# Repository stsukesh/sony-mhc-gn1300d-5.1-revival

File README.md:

# Sony MHC-GN1300D 5.1 Audio System Revival

A complete, production-grade revival and modernization system for the vintage **Sony MHC-GN1300D Mini Hi-Fi Component System** (and similar 5.1 home theater units). 

This project replaces dead, obsolete hybrid IC amplifier boards (STK modules) and failing logic boards with a **single custom 150×200mm 2-layer PCB**, modern high-efficiency Class-D amplification, an active analog crossover, an ESP32 IoT control hub, and a multi-layer hardware-software fail-proof protection engine.

---

## Key System Specifications

| Parameter | Specification |
|---|---|
| **Form Factor** | 150 mm × 200 mm 2-Layer PCB (Lion Circuits India compatible) |
| **Output Channels** | 5.1 Channels (Front L/R, Surround L/R, Center, Subwoofer) |
| **Amplifier ICs** | 3× Texas Instruments TPA3116D2 Class-D stereo amplifiers |
| **Crossover Network** | Analog 2nd-order Sallen-Key active crossover (80 Hz cutoff, 3× NE5532 op-amps) |
| **Microcontroller** | ESP32-WROOM-32 (240 MHz dual-core, WiFi, BLE) |
| **Volume Control** | Microchip MCP4252 SPI 8-bit dual digital potentiometer |
| **Input Selection** | TI CD4052 dual 4:1 multiplexer (Bluetooth, 3.5mm AUX, USB Audio) |
| **Local Interface** | 2.42" SSD1309 SPI OLED (128×64) + Rotary Encoder + TSOP1738 IR Remote |
| **Connectivity** | WiFi AP (`Sony5.1-Revival`) & STA, Web dashboard, REST API, WebSockets, UART CLI |
| **Power Supply** | 230V AC mains input, internal 18V AC toroidal transformer, KBU810 bridge + 2× 4700µF filter (~24V DC), LM2596-5.0 buck, AMS1117-3.3 LDO, TLE2426 virtual ground |
| **Protection** | 5-layer fail-safe: DC offset detect, heatsink NTC thermal sensing, SPST 10A relay, polyfuses, HW pull-downs |
| **Total Build Cost** | ~₹9,124 INR (~$110 USD) — well within ₹10,000 budget |

---

## 5-Layer Fail-Proof Protection Engine

1. **Layer 1 — Hardware Fail-Safe Defaults:**
   - Amps default to hardware-muted via 10kΩ pull-downs on `/MUTE`.
   - Speaker 24V supply is isolated via normally-open relay `K1`. If the ESP32 crashes or loses power, speakers remain 100% silent and protected.
2. **Layer 2 — Hardware Watchdog Timer (TWDT):**
   - 10-second timeout automatically hard-resets the MCU into a safe state if firmware hangs.
3. **Layer 3 — Timed Startup Sequencing:**
   - 3-second power-on delay to stabilize rails, fault pin verification, relay closure, and a 500ms delayed un-mute to completely eliminate turn-on thumps.
4. **Layer 4 — Continuous Runtime ADC Telemetry:**
   - Sub-millivolt DC offset detection on speaker outputs (`GPIO36`).
   - Heatsink thermal monitoring via 10kΩ NTC thermistor (`GPIO35`): auto-attenuation at >60°C, emergency shutdown at >80°C.
   - Continuous latching on all 3 TPA3116D2 `/FAULT` lines (`GPIO32`, `GPIO33`, `GPIO34`).
5. **Layer 5 — Output Polyfuse Current Clamping:**
   - 2A resettable PTC polyfuses in series with speaker outputs to protect against external voice coil shorts.

---

## Repository Structure

```
├── hardware/
│   └── sony-5.1-revival/
│       ├── sony-5.1-revival.kicad_pro      # KiCad 10 Project File
│       ├── sony-5.1-revival.kicad_sch      # Top-level Hierarchical Schematic
│       ├── power_supply.kicad_sch          # Sheet 1: AC-DC, Buck, LDO & Virtual Ground
│       ├── amplifier.kicad_sch             # Sheet 2: 3× TPA3116D2 Class-D Stages
│       ├── crossover_input.kicad_sch       # Sheet 3: CD4052 Mux, MCP4252 Vol & NE5532 Filters
│       ├── controller.kicad_sch            # Sheet 4: ESP32, OLED, Rotary, IR, USB UART
│       ├── protection.kicad_sch            # Sheet 5: Relay, NTC, DC Sense, Screw Terminals
│       ├── sony-5.1-revival.kicad_pcb      # Fully placed & routed 150×200mm 2-layer PCB
│       ├── sony-5.1-revival-schematic.pdf  # Clean multi-page vectorized schematic
│       ├── pcb_preview_top.png             # High-resolution 300 DPI board render
│       ├── BOM.csv                         # Itemized 38-part Bill of Materials (INR)
│       ├── lioncircuits_fab_files.zip      # Ready-to-upload Gerber/Drill manufacturing zip
│       ├── gerbers/                        # Unpacked Gerber and drill files
│       └── libs/                           # Custom KiCad symbol library
├── firmware/
│   ├── platformio.ini                      # PlatformIO build configuration for ESP32
│   ├── src/
│   │   ├── main.cpp                        # System orchestrator and startup sequencing
│   │   ├── config.h                        # System parameters and protection thresholds
│   │   ├── pin_definitions.h               # Complete GPIO & SPI pin map
│   │   ├── audio_controller.cpp / .h       # MCP4252 digital pot and CD4052 mux driver
│   │   ├── display_manager.cpp / .h        # 2.42" SSD1309 OLED graphics engine
│   │   ├── input_handler.cpp / .h          # Rotary encoder (ISR) & NEC IR remote decoder
│   │   ├── protection.cpp / .h             # 5-layer telemetry and emergency shutdown engine
│   │   ├── web_server.cpp / .h             # Async web server, REST API & WebSockets
│   │   ├── serial_cmd.cpp / .h             # 115,200 baud UART command interface
│   │   └── wifi_manager.cpp / .h           # Dual AP/STA WiFi manager with NVS storage
│   └── data/
│       └── index.html                      # Responsive dark-theme browser dashboard
├── tools/                                  # Project automation, simulation & generators
├── MHC-GN1300D-Revival-Master-Plan.md      # Comprehensive architecture & wiring manual
├── Sony-5.1-Revival-Implementation-Report.md # Full design report and telemetry analysis
├── Sony-5.1-Revival-OEM-Service-Manual.md  # OEM-grade repair, schematics & troubleshooting guide
└── Lion-Circuits-Fabrication-and-Assembly-Manual.md # PCB fabrication & bench checkout guide
```

---

## PCB Fabrication Guide (Lion Circuits India)

The board layout is pre-configured and checked against Lion Circuits manufacturing capabilities:

1. Upload `hardware/sony-5.1-revival/lioncircuits_fab_files.zip` directly to [LionCircuits.com](https://www.lioncircuits.com/).
2. Specify the fabrication parameters:
   - **Dimensions:** 150.0 mm × 200.0 mm
   - **Layers:** 2 Layers
   - **PCB Thickness:** 1.6 mm
   - **Copper Weight:** 1 oz (35 µm)
   - **Solder Mask:** Green (or Matte Black)
   - **Silkscreen:** White
   - **Surface Finish:** HASL Lead-Free
3. Minimum trace width used: **0.30 mm** (Signal), **1.00 mm - 3.50 mm** (Power / Speaker).
4. Minimum clearance: **0.25 mm** (High-voltage AC clearance: > 5.0 mm).

---

## Firmware Setup & Flashing

### Prerequisites
- [PlatformIO Core](https://platformio.org/install/cli) or VS Code with PlatformIO IDE extension.
- Micro-USB cable connected to the ESP32 development board.

### Build and Upload
```bash
cd firmware

# Build firmware binary
pio run

# Upload to ESP32 (auto-detects port)
pio run -t upload

# Upload SPIFFS/LittleFS web dashboard assets
pio run -t uploadfs

# Open serial terminal monitor (115200 baud)
pio device monitor -b 115200
```

### Serial Control Interface
Connect any serial terminal at `115200 baud, 8-N-1`:
- `VOL <0-255>`: Set volume directly
- `VOL+` / `VOL-`: Adjust volume up/down by 5 steps
- `INPUT <BT|AUX|USB>`: Switch input audio source
- `MUTE`: Toggle mute
- `POWER`: Toggle 24V amplifier relay
- `STATUS`: Print full JSON telemetry report
- `PROTECTION`: Display ADC offsets, temperatures, and fault latch states

---

## License & Safety Disclaimer

**Mains Voltage Warning:** This design incorporates 230V AC mains input. Always disconnect AC mains before touching any part of the primary side. Use an isolation transformer during bench testing.

Licensed under the [MIT License](LICENSE).

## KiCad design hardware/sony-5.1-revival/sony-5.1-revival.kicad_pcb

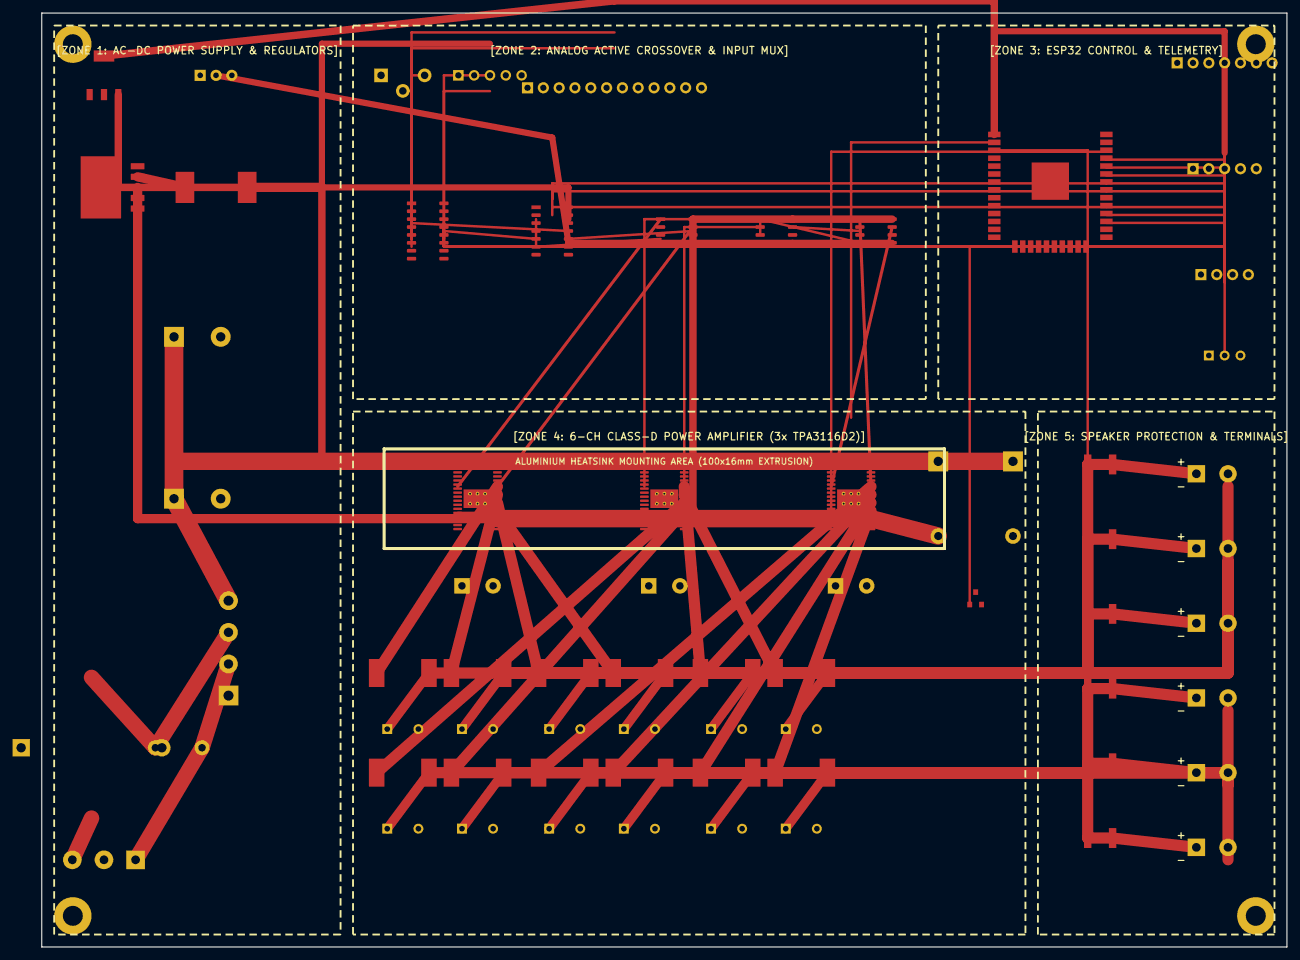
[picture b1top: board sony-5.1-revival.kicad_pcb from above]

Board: 2 copper layers, 200.0 x 150.0 mm, 71 parts (0 on the bottom side), 52 nets.

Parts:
BR1: KBU810_8A; Diode_Bridge_Vishay_KBU
C1, C2: 4700uF_35V; CP_Radial_D18.0mm_P7.50mm
C_BULK1, C_BULK2, C_BULK3: CP_Radial_D12.5mm_P5.00mm
C_O1, C_O2, C_O3, C_O4, C_O5, C_O6, C_O7, C_O8, C_O9, C_O10, C_O11, C_O12: C_Rect_L7.2mm_W4.5mm_P5.00mm_FKS2_FKP2_MKS2_MKP2
F1: 3A_250V; Fuseholder_5x20mm
H: MountingHole_3.2mm_M3
H#2, H#3, H#4: MountingHole_3.2mm_M3
J_AC: 230V_AC_IN; TerminalBlock_1x03_P5.08mm
J_AUX: AUX_3.5mm; Jack_3.5mm_CUI_SJ1-3523N_Horizontal
J_CTRL: UART_CONTROL; PinHeader_1x04_P2.54mm_Vertical
J_ENC: ROTARY_ENCODER; PinHeader_1x05_P2.54mm_Vertical
J_OLED: 2.42_SSD1309_SPI; PinHeader_1x07_P2.54mm_Vertical
J_SPK_C: CENTER; TerminalBlock_1x02_P5.08mm
J_SPK_FL: FRONT_LEFT; TerminalBlock_1x02_P5.08mm
J_SPK_FR: FRONT_RIGHT; TerminalBlock_1x02_P5.08mm
J_SPK_SL: SURROUND_LEFT; TerminalBlock_1x02_P5.08mm
J_SPK_SR: SURROUND_RIGHT; TerminalBlock_1x02_P5.08mm
J_SPK_SUB: SUBWOOFER; TerminalBlock_1x02_P5.08mm
J_USB_IN: USB_AUDIO_DAC; PinHeader_1x05_P2.54mm_Vertical
K1: RELAY_10A_24V; Relay_SPST_SANYOU_SRD_Series_Form_A
L1, L2, L3, L4, L5, L6, L7, L8, L9, L10, L11, L12: 22uH_5A; L_10.4x10.4_H4.8
L_BUCK: 33uH_3A; L_12x12mm_H8mm
PF_C: 2A_PTC; Fuse_1812_4532Metric
PF_FL: 2A_PTC; Fuse_1812_4532Metric
PF_FR: 2A_PTC; Fuse_1812_4532Metric
PF_SL: 2A_PTC; Fuse_1812_4532Metric
PF_SR: 2A_PTC; Fuse_1812_4532Metric
PF_SUB: 2A_PTC; Fuse_1812_4532Metric
Q1: SOT-23
RV1: 14D431K; RV_Disc_D14mm_W4.5mm_P7.5mm
U_AMP1: TPA3116_FL_FR; HTSSOP-32-1EP_6.1x11mm_P0.65mm_EP3.1x6.1mm_ThermalVias
U_AMP2: TPA3116_SL_SR; HTSSOP-32-1EP_6.1x11mm_P0.65mm_EP3.1x6.1mm_ThermalVias
U_AMP3: TPA3116_C_SUB; HTSSOP-32-1EP_6.1x11mm_P0.65mm_EP3.1x6.1mm_ThermalVias
U_BT: QCC3008_BT5.0; PinHeader_1x12_P2.54mm_Vertical
U_BUCK: LM2596-5.0; TO-263-5_TabPin3
U_IR: IRReceiver_Vishay_CAST-3pin
U_LDO: AMS1117-3.3; SOT-223-3_TabPin2
U_MCU: ESP32-WROOM-32
U_MUX: CD4052_MUX; SOIC-16_3.9x9.6mm_P1.27mm
U_OP1: NE5532_HPF; SOIC-8_3.9x4.8mm_P1.27mm
U_OP2: NE5532_SUM; SOIC-8_3.9x4.8mm_P1.27mm
U_OP3: NE5532_LPF_C; SOIC-8_3.9x4.8mm_P1.27mm
U_VGND: TLE2426; TO-92_Inline
U_VOL: MCP4252_POT; SOIC-14_3.9x8.4mm_P1.27mm

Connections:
AC_LIVE: BR1.2, F1.1, F1.2, J_AC.1, RV1.1
AC_NEUTRAL: BR1.3, J_AC.3, RV1.2
AUDIO_L_RAW: U_MUX.13, U_VOL.5
AUDIO_R_RAW: U_MUX.3, U_VOL.10
BT_KEY: U_BT.5, U_MCU.30
BT_OUT_L: U_BT.3, U_MUX.12
BT_OUT_R: U_BT.4, U_MUX.1
ENC_A: J_ENC.5, U_MCU.36
ENC_B: J_ENC.4, U_MCU.35
ENC_SW: J_ENC.3, U_MCU.34
GND: BR1.4, C1.2, C2.2, C_BULK1.2, C_BULK2.2, C_BULK3.2, C_O1.2, C_O2.2, C_O3.2, C_O4.2, C_O5.2, C_O6.2, C_O7.2, C_O8.2, C_O9.2, C_O10.2, C_O11.2, C_O12.2, H.1, H#2.1, H#3.1, H#4.1, J_AC.2, J_AUX.1, J_CTRL.4, J_ENC.1, J_OLED.1, J_USB_IN.2, J_USB_IN.5, Q1.2, U_AMP1.1, U_AMP1.5, U_AMP1.6, U_AMP1.9, U_AMP1.10, U_AMP1.11, U_AMP1.13, U_AMP1.15, U_AMP1.16, U_AMP1.17, U_AMP1.19, U_AMP1.25, U_AMP1.31, U_AMP1.33, U_AMP2.1, U_AMP2.5, U_AMP2.6, U_AMP2.9, U_AMP2.10, U_AMP2.11, U_AMP2.13, U_AMP2.15, U_AMP2.16, U_AMP2.17, U_AMP2.19, U_AMP2.25, U_AMP2.31, U_AMP2.33, U_AMP3.1, U_AMP3.5, U_AMP3.6, U_AMP3.9, U_AMP3.10, U_AMP3.11, U_AMP3.13, U_AMP3.15, U_AMP3.16, U_AMP3.17, U_AMP3.19, U_AMP3.25, U_AMP3.31, U_AMP3.33, U_BT.2, U_BT.6, U_BT.7, U_BT.8, U_BT.9, U_BT.10, U_BT.11, U_BT.12, U_BUCK.3, U_BUCK.5, U_BUCK.6, U_IR.2, U_LDO.1, U_MCU.1, U_MCU.4, U_MCU.7, U_MCU.8, U_MCU.9, U_MCU.10, U_MCU.11, U_MCU.12, U_MCU.13, U_MCU.14, U_MCU.16, U_MCU.17, U_MCU.18, U_MCU.21, U_MCU.22, U_MCU.25, U_MCU.26, U_MCU.31, U_MCU.39, U_MUX.4, U_MUX.6, U_MUX.7, U_MUX.8, U_MUX.11, U_OP1.4, U_OP2.4, U_OP3.4, U_VGND.3, U_VOL.4
HPF_L: U_AMP1.4, U_OP1.1, U_OP1.2, U_OP2.2
HPF_R: U_AMP1.14, U_OP1.6, U_OP1.7
IR_RECV: U_IR.1, U_MCU.37
J_AUX_L: J_AUX.2, U_MUX.14
J_AUX_R: J_AUX.3, U_MUX.5
MUTE_ALL: U_AMP1.12, U_AMP2.12, U_AMP3.12, U_MCU.38
MUX_A: U_MCU.24, U_MUX.10
OLED_CS: J_OLED.7, U_MCU.20
OLED_DC: J_OLED.6, U_MCU.19
OUT_CENTER: U_AMP3.4, U_OP3.7
OUT_C_N: C_O10.1, J_SPK_C.2, L10.1, L10.2, U_AMP3.18, U_AMP3.24
OUT_C_P: C_O9.1, J_SPK_C.1, L9.1, L9.2, PF_C.1, PF_C.2, U_AMP3.20, U_AMP3.21
OUT_FL_N: C_O2.1, J_SPK_FL.2, L2.1, L2.2, U_AMP1.18, U_AMP1.24
OUT_FL_P: C_O1.1, J_SPK_FL.1, L1.1, L1.2, PF_FL.1, PF_FL.2, U_AMP1.20, U_AMP1.21
OUT_FR_N: C_O4.1, J_SPK_FR.2, L4.1, L4.2, U_AMP1.26, U_AMP1.32
OUT_FR_P: C_O3.1, J_SPK_FR.1, L3.1, L3.2, PF_FR.1, PF_FR.2, U_AMP1.29, U_AMP1.30
OUT_SL_N: C_O6.1, J_SPK_SL.2, L6.1, L6.2, U_AMP2.18, U_AMP2.24
OUT_SL_P: C_O5.1, J_SPK_SL.1, L5.1, L5.2, PF_SL.1, PF_SL.2, U_AMP2.20, U_AMP2.21
OUT_SR_N: C_O8.1, J_SPK_SR.2, L8.1, L8.2, U_AMP2.26, U_AMP2.32
OUT_SR_P: C_O7.1, J_SPK_SR.1, L7.1, L7.2, PF_SR.1, PF_SR.2, U_AMP2.29, U_AMP2.30
OUT_SUB: U_AMP3.14, U_OP3.1, U_OP3.2
OUT_SUB_N: C_O12.1, J_SPK_SUB.2, L12.1, L12.2, U_AMP3.26, U_AMP3.32
OUT_SUB_P: C_O11.1, J_SPK_SUB.1, L11.1, L11.2, PF_SUB.1, PF_SUB.2, U_AMP3.29, U_AMP3.30
RELAY_CTRL: K1.2, Q1.1, Q1.3, U_MCU.15
SPI_MISO: U_MCU.32, U_VOL.13
SPI_MOSI: J_OLED.4, U_MCU.29, U_VOL.3
SPI_SCK: J_OLED.3, U_MCU.33, U_VOL.2
SUM_CENTER: U_OP2.1, U_OP3.6
SUM_SUB_RAW: U_OP2.7, U_OP3.3
UART_RX: J_CTRL.3, U_MCU.27
UART_TX: J_CTRL.2, U_MCU.28
USB_L: J_USB_IN.3, U_MUX.15
USB_R: J_USB_IN.4, U_MUX.2
VCC_3V3: J_CTRL.1, J_ENC.2, J_OLED.2, J_OLED.5, U_AMP1.7, U_AMP2.7, U_AMP3.7, U_BT.1, U_IR.3, U_LDO.2, U_LDO.4, U_MCU.2, U_MCU.3
VCC_5V: J_USB_IN.1, K1.1, L_BUCK.1, L_BUCK.2, U_BUCK.2, U_BUCK.4, U_LDO.3, U_VOL.11, U_VOL.12, U_VOL.14
VCC_24V: C_BULK1.1, C_BULK2.1, C_BULK3.1, K1.4, U_AMP1.2, U_AMP1.8, U_AMP1.22, U_AMP1.23, U_AMP1.27, U_AMP1.28, U_AMP2.2, U_AMP2.8, U_AMP2.22, U_AMP2.23, U_AMP2.27, U_AMP2.28, U_AMP3.2, U_AMP3.8, U_AMP3.22, U_AMP3.23, U_AMP3.27, U_AMP3.28, U_BUCK.1, U_MUX.16, U_OP1.8, U_OP2.8, U_OP3.8, U_VGND.1
VCC_24V_RAW: BR1.1, C1.1, C2.1, K1.3
VGND_12V: U_OP2.3, U_OP2.5, U_OP3.5, U_VGND.2, U_VOL.7, U_VOL.8
VOL_CS: U_MCU.23, U_VOL.1
VOL_L: U_OP1.3, U_OP2.6, U_VOL.6
VOL_R: U_OP1.5, U_VOL.9

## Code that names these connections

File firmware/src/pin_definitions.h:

#pragma once
#include <Arduino.h>

constexpr uint8_t PIN_STATUS_LED = 2;
constexpr uint8_t PIN_OLED_DC = 4;
constexpr uint8_t PIN_OLED_CS = 5;
constexpr uint8_t PIN_OLED_RST = -1; // Assuming connected to EN/RST

constexpr uint8_t PIN_RELAY_CTRL = 12;
constexpr uint8_t PIN_MUTE_ALL = 13;

constexpr uint8_t PIN_IR_RECV = 14;
constexpr uint8_t PIN_ENC_A = 15;
constexpr uint8_t PIN_ENC_B = 16;
constexpr uint8_t PIN_ENC_SW = 17;

constexpr uint8_t PIN_SPI_SCK = 18;
constexpr uint8_t PIN_SPI_MISO = 19;
constexpr uint8_t PIN_SPI_MOSI = 23;

constexpr uint8_t PIN_VOL_CS = 25;
constexpr uint8_t PIN_MUX_A = 26;
constexpr uint8_t PIN_MUX_B = 27;

constexpr uint8_t PIN_FAULT1 = 32;
constexpr uint8_t PIN_FAULT2 = 33;
constexpr uint8_t PIN_FAULT3 = 34;

constexpr uint8_t PIN_NTC_ADC = 35;
constexpr uint8_t PIN_DC_OFFSET_ADC = 36;

constexpr uint8_t PIN_BT_KEY = 21;

constexpr uint8_t PIN_UART_TX = 1;
constexpr uint8_t PIN_UART_RX = 3;

constexpr uint32_t SPI_SPEED_OLED = 8000000;
constexpr uint32_t SPI_SPEED_MCP4252 = 1000000;

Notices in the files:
README.md:
License: MIT
